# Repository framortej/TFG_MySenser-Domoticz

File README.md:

# TFG_MySenser-Domoticz
Repositorio del TFG "Desarrollo de sistemas domóticos basados en la red MySensor"

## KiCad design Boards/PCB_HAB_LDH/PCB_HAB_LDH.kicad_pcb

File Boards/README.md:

All projects are hosted at https://easyeda.com 
The website of the project is:
https://easyeda.com/framortej/desarrollo-de-sistemas-dom-ticos-basados-en-la-red-mysensor

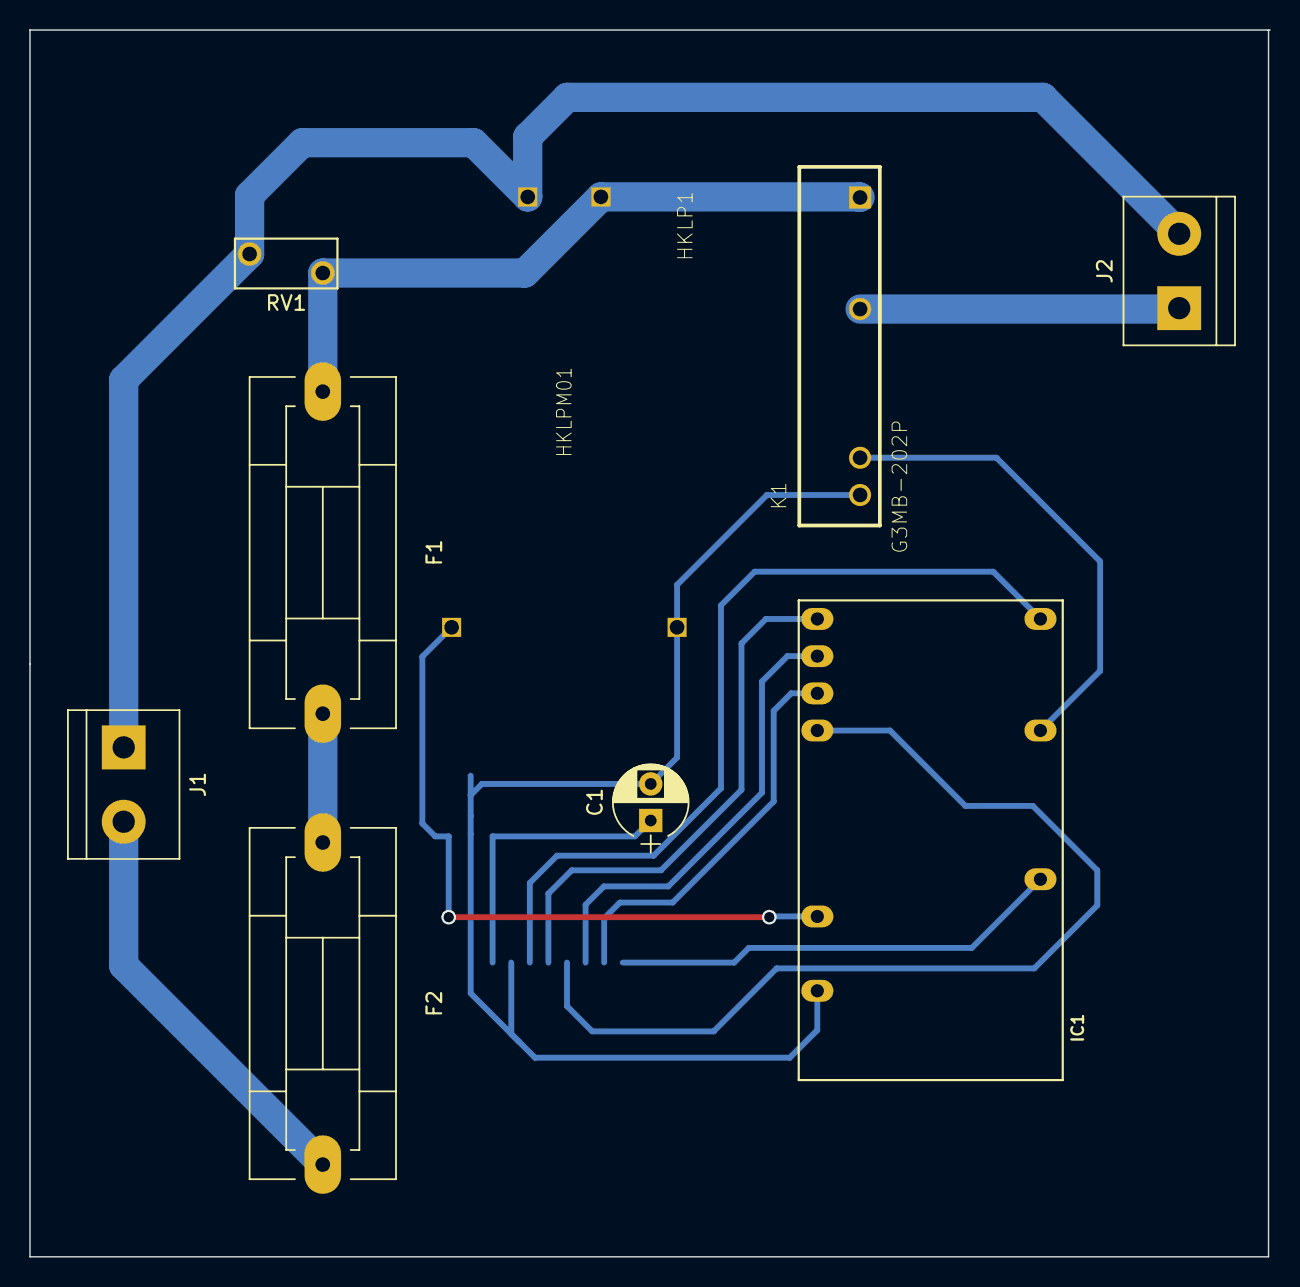
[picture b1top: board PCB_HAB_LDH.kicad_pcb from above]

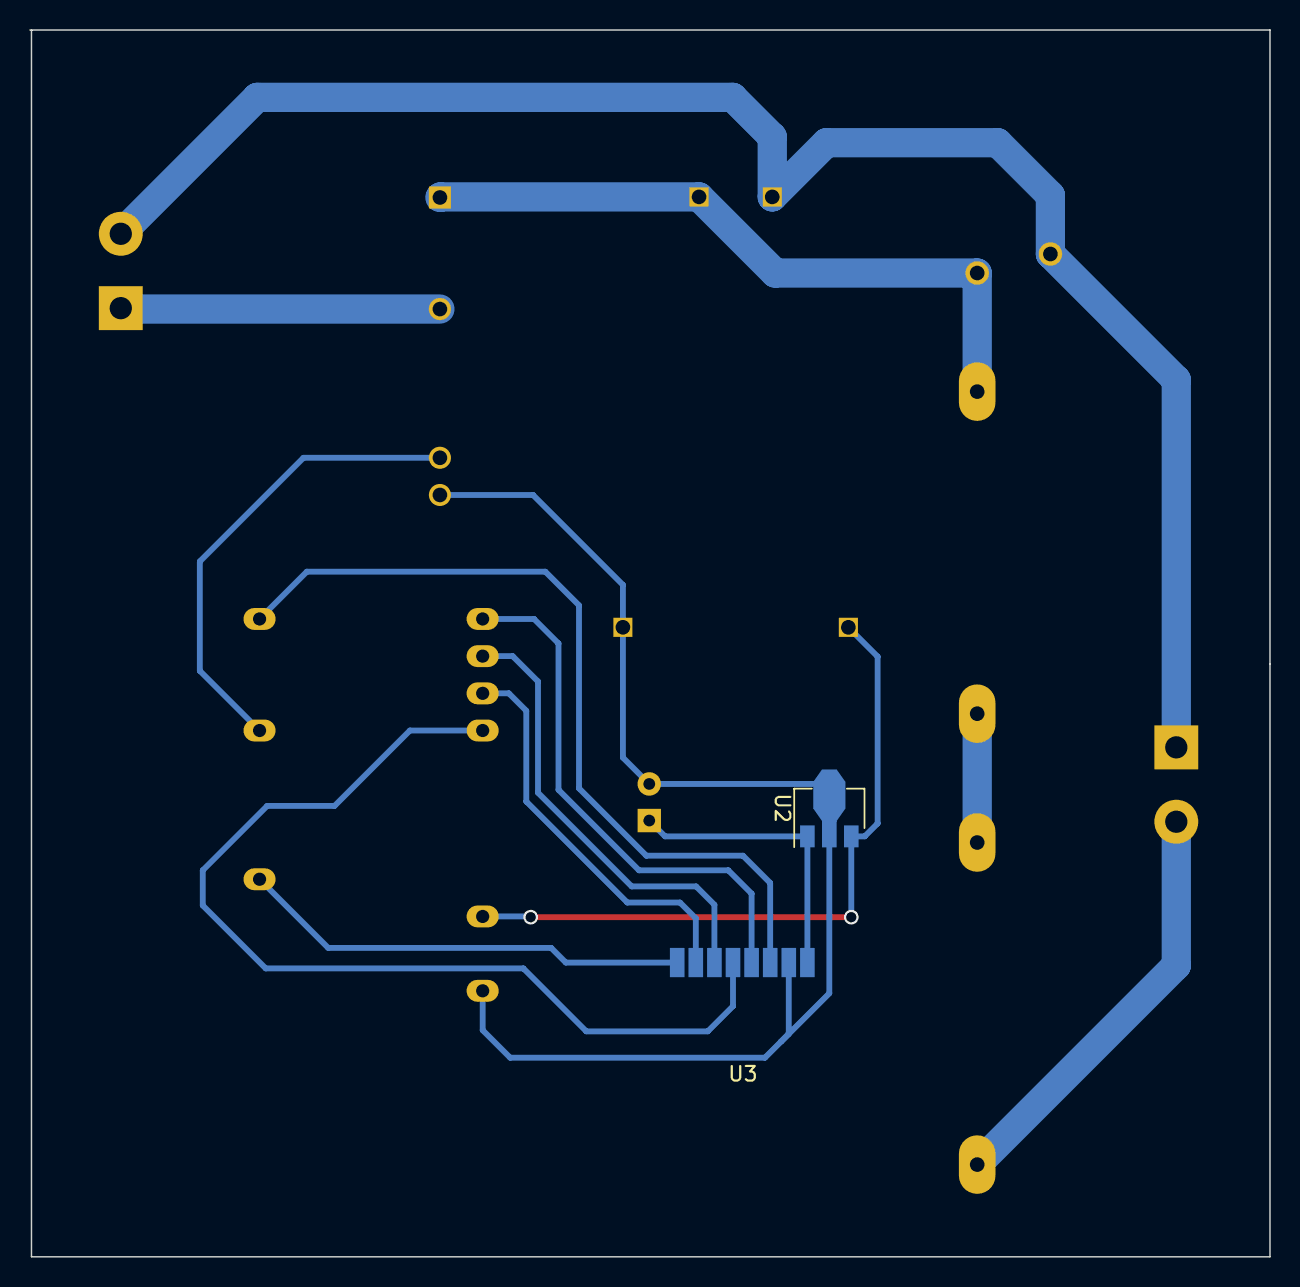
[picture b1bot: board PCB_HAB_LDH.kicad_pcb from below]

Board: 2 copper layers, 84.7 x 83.8 mm, 11 parts (2 on the bottom side), 15 nets.

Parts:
C1: CP1; CP_Radial_D5.0mm_P2.50mm
F1: Fusible; Fuseholder5x20_horiz_SemiClosed_Casing10x25mm
F2: Termo; Fuseholder5x20_horiz_SemiClosed_Casing10x25mm
HKLP1: HKLPM01
IC1: ArduinoProMini; pro_mini_LDH_0.9Pads
J1: AC INPUT; TerminalBlock_bornier-2_P5.08mm
J2: AC OUTPUT; TerminalBlock_bornier-2_P5.08mm
K1: G3MB-202P; RELAY_G3MB-202P
RV1: Varistor; RV_Disc_D7_W3.4_P5
U2: L78L33_SOT89; SOT-89-3
U3: NRF24L01; NRF24L01-SMD

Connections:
/a1: IC1.13, U3.4
/a2: IC1.5, U3.8
/a3: IC1.12, U3.3
/a4: IC1.15, U3.7
/a5: IC1.14, U3.6
/a6: IC1.16, U3.5
unnamed: C1.1, U2.1, U3.2
unnamed: C1.2, HKLP1.P$3, IC1.23, K1.4, U2.2, U3.1
unnamed: F1.1, HKLP1.P$1, K1.1, RV1.2
unnamed: F1.2, F2.1
unnamed: F2.2, J1.2
unnamed: HKLP1.P$2, J1.1, J2.2, RV1.1
unnamed: HKLP1.P$4, IC1.21, U2.3
unnamed: IC1.9, K1.3
unnamed: J2.1, K1.2

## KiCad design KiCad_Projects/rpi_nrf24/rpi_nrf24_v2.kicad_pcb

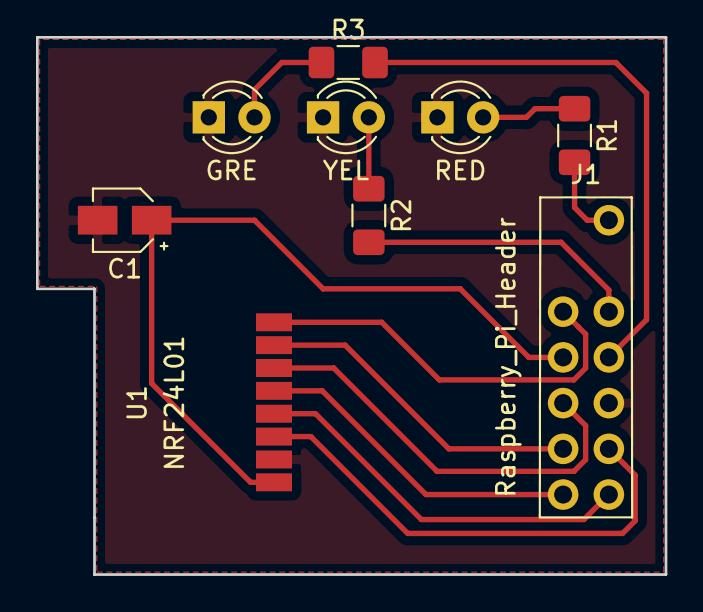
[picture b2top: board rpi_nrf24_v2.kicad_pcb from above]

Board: 2 copper layers, 34.9 x 29.8 mm, 9 parts (0 on the bottom side), 14 nets.

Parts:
C1: CP1; CP_Elec_3x5.3
D1: RED; LED_D3.0mm
D2: YEL; LED_D3.0mm
D3: GRE; LED_D3.0mm
J1: Raspberry_Pi_Header; PinHeader_nrf24+leds
R1, R2, R3: R; R_1206_3216Metric_Pad1.42x1.75mm_HandSolder
U1: NRF24L01; NRF24L01-SMD

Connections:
unnamed: C1.1, J1.17, U1.2
unnamed: C1.2, D1.1, D2.1, D3.1, J1.20, U1.1
unnamed: D1.2, R1.1
unnamed: D2.2, R2.1
unnamed: D3.2, R3.1
unnamed: J1.12, R1.2
unnamed: J1.15, U1.8
unnamed: J1.16, R2.2
unnamed: J1.18, R3.2
unnamed: J1.19, U1.6
unnamed: J1.21, U1.7
unnamed: J1.22, U1.3
unnamed: J1.23, U1.5
unnamed: J1.24, U1.4

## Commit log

2019-07-14 Creado el proyecto para la P1_ElectricalManagement
2019-07-22 P1, P2 and P3 fisnish. I will Upload it soon!
2019-08-30 Pre-release v0.9
2019-08-30 Sync PCSERVER
2019-09-09 V0.9.9
2019-09-10 Pre-release v0.9.9.9
2019-09-10 Pre-release
2019-09-12 v1.0 Pre-release -> Minor changes in some .ino files
2019-09-12 Cleaned repository
2019-09-19 Update some files Add TFG presentation
